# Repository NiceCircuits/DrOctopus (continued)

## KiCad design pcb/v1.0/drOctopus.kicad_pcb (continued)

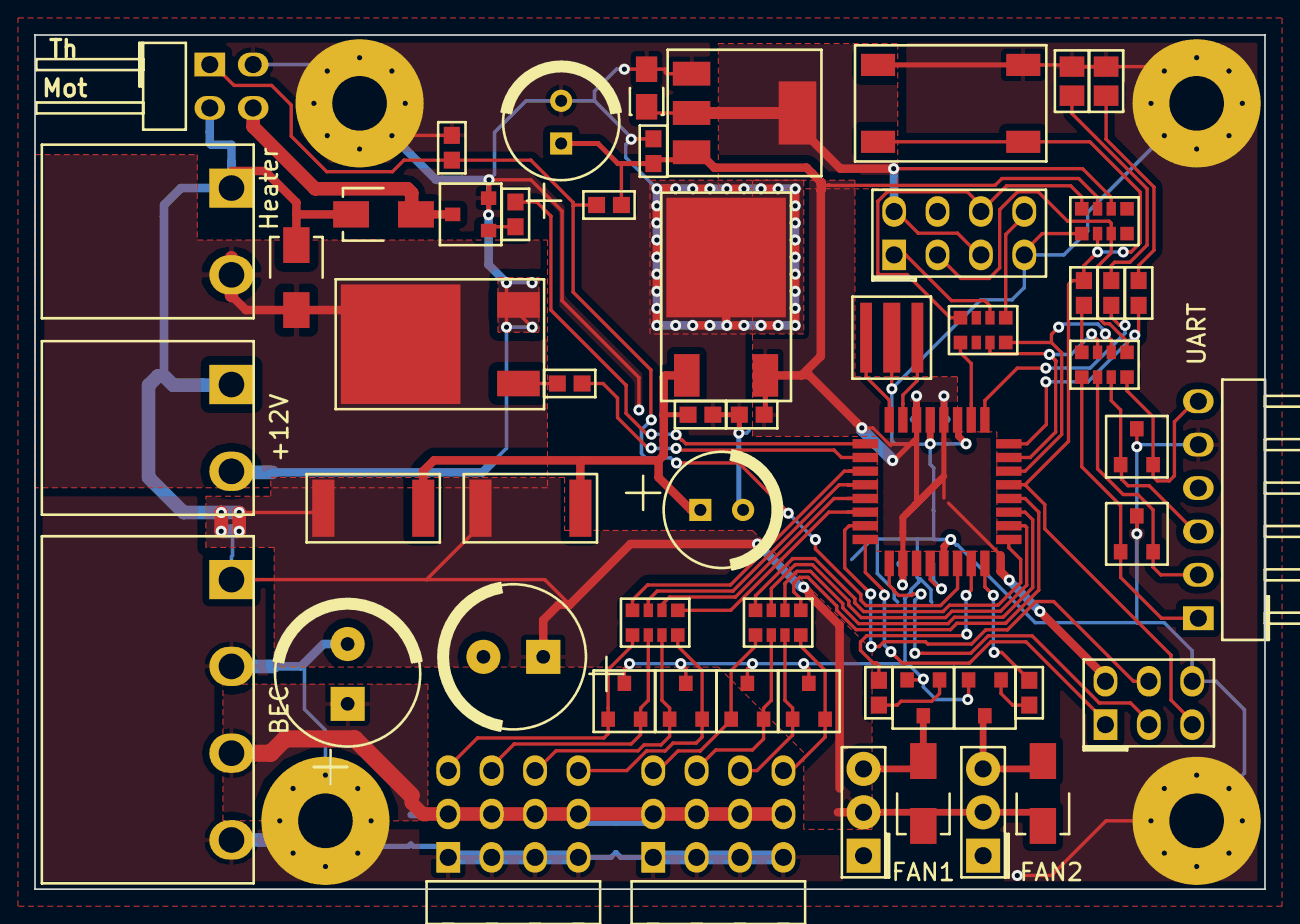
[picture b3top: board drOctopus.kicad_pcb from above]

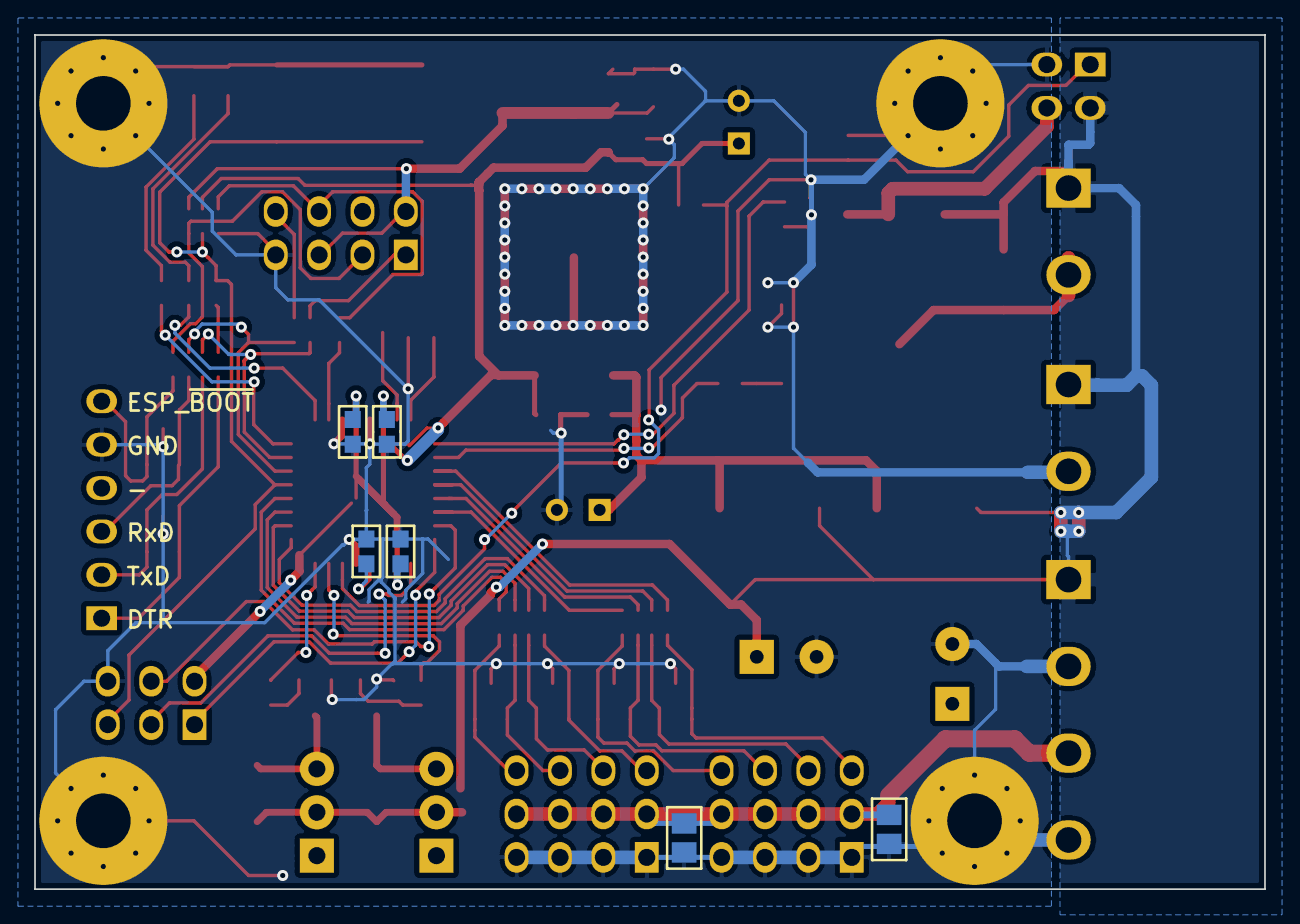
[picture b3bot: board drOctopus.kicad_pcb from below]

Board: 2 copper layers, 72.0 x 50.0 mm, 72 parts (9 on the bottom side), 58 nets.

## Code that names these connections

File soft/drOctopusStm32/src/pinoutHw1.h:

/**
 ******************************************************************************
 * @file    pinoutHw1.h
 * @author  piotr@nicecircuits.com
 * @date    2016-02-07
 * @brief   Pinout file for HW 1
 ******************************************************************************
 */
#ifndef PINOUTHW0_H_
#define PINOUTHW0_H_

#include <inttypes.h>
#include "stm32f0xx.h"
#if defined(HW_VERSION) && HW_VERSION == HW_VERSION1
/**
 * Initialize basic peripheral registers (mostly clocks and alternative pin
 * functions).
 * @return 0 if OK.
 */
uint_fast8_t portInit(void);

/**
 * Initialize ADC - version specific function.
 * @param adcBuffer ADC DMA buffer
 * @return 0 if OK
 */
uint_fast8_t adcInitVersionSpecific(uint16_t *adcBuffer);

/******************************************************************************
 * Pinout
 ******************************************************************************/
// ---------- Debug port ----------
#define DEBUG_USART USART2
#define DEBUG_GPIO GPIOA
#define DEBUG_RX_PIN GPIO_Pin_3
#define DEBUG_TX_PIN GPIO_Pin_2
#define DEBUG_DMA DMA1_Channel4
/// Debug DMA transfer complete flag.
#define DEBUG_DMA_TC_FLAG DMA1_FLAG_TC4

// ---------- LEDs ----------
/// Number of LEDs present.
#define LED_NUMBER 2
#define LED_GPIOS {GPIOB, GPIOB}
#define LED_PINS {GPIO_Pin_12, GPIO_Pin_13}
#define LED_ACTIVE_STATES {1,1}

// ---------- PWM ----------
#define PWM_TIMER TIM3
#define PWM_GPIO GPIOC
// PWM channels: motor, heater, fan, fan2
#define PWM_PINS (GPIO_Pin_9 | GPIO_Pin_6 | GPIO_Pin_7 | GPIO_Pin_8)
#define PWM_CHANNELS {&(TIM3->CCR4), &(TIM3->CCR1), &(TIM3->CCR2), &(TIM3->CCR3)}
#define PWM_IRQ TIM3_IRQn
#define PWM_IRQ_HANDLER TIM3_IRQHandler

// ---------- servos ----------
#define SERVO_NUMBER (8)
#define SERVO_TIMERS_NUMBER (4)
#define SERVO_TIMERS {TIM1, TIM15, TIM16, TIM17}
#define SERVO_GPIOS {GPIOA, GPIOA, GPIOA, GPIOA, GPIOB, GPIOB, GPIOB, GPIOB}
#define SERVO_PINS {GPIO_Pin_8, GPIO_Pin_9, GPIO_Pin_10, GPIO_Pin_11, GPIO_Pin_8, GPIO_Pin_15, GPIO_Pin_14, GPIO_Pin_9}
#define SERVO_CHANNELS {&(TIM1->CCR1), &(TIM1->CCR2), &(TIM1->CCR3), &(TIM1->CCR4), &(TIM16->CCR1), &(TIM15->CCR2), &(TIM15->CCR1), &(TIM17->CCR1)}
#define SERVO_IRQ TIM1_BRK_UP_TRG_COM_IRQn
#define SERVO_IRQ_HANDLER TIM1_BRK_UP_TRG_COM_IRQHandler

// ---------- ADC ----------
#define ADC_ADC ADC1
/// Number of ADC channels.
#define ADC_NUMBER (8)
// ADC channels: heater_sig, bts_fb_sig, thermistors from 0
#define ADC_GPIOS {GPIOA, GPIOC, GPIOA, GPIOA, GPIOC, GPIOC, GPIOC, GPIOC}
#define ADC_PINS {GPIO_Pin_5, GPIO_Pin_5, GPIO_Pin_6, GPIO_Pin_7, GPIO_Pin_4, GPIO_Pin_1, GPIO_Pin_2, GPIO_Pin_3}
#define ADC_CHANNELS {ADC_Channel_5, ADC_Channel_15, ADC_Channel_6, ADC_Channel_7, ADC_Channel_14, ADC_Channel_11, ADC_Channel_12, ADC_Channel_13}
#define ADC_DMA DMA1_Channel1
/// ADC conversion trigger event: Timer 3
#define ADC_TRIGGER (ADC_ExternalTrigConv_T3_TRGO)
#define ADC_FLAG_RDY ADC_FLAG_ADRDY
#define ADC_SAMPLE_TIME ADC_SampleTime_55_5Cycles

// ---------- I2C ----------
#define I2C I2C2
// I2C pins: SDA, SCL
#define I2C_GPIOS {GPIOB, GPIOB}
#define I2C_PINS {GPIO_Pin_11, GPIO_Pin_10}

// ---------- delay ----------
#define DELAY_TIMER TIM2

// ---------- ESP8266 ----------
#define ESP_USART USART3
#define ESP_GPIO GPIOC
#define ESP_RX_PIN GPIO_Pin_11
#define ESP_TX_PIN GPIO_Pin_10
#define ESP_EN_GPIO GPIOB
#define ESP_EN_PIN GPIO_Pin_1
#define ESP_BOOT_GPIO GPIOB
#define ESP_BOOT_PIN GPIO_Pin_0
#define ESP_TX_DMA DMA1_Channel2
/// ESP8266 DMA transmit complete flag.
#define ESP_DMA_TX_TC_FLAG DMA1_FLAG_TC2
#define ESP_IRQHandler USART3_6_IRQHandler
#define ESP_IRQ USART3_6_IRQn
#else // #if defined(HW_VERSION) && HW_VERSION == HW_VERSION1
#error "Invalid pinout file used or HW version not defined!"
#endif
#endif /* PINOUTHW0_H_ */

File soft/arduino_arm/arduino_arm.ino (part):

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#include <EEPROM.h>
#define HDServoMode 20
#define SerialInterfaceSpeed 115200    // Serial interface Speed
#define THERM A7
#define HEAT 6
#define MOT 5
#define LED 3

static unsigned int iCount;
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void setup()
{
 uint8_t id = EEPROM.read(10);
 pinMode(HEAT, OUTPUT);
  pinMode(MOT, OUTPUT);
 pinMode(THERM, INPUT);
 if (id==4)
 {
  OutPortTable = OutPortTable4;
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
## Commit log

2014-08-02 Start design
2014-08-03 Select motors
2014-08-03 Sketches
2014-10-09 Start 3D modeling
2014-10-10 Straight version
2014-10-10 3D design
2014-10-12 Continue 3D modeling
2014-10-13 Fix small issues
2014-10-20 3D modeling
2014-10-21 Soft
2014-10-22 Rename and generate production files
2015-08-27 Nowa PCB - wersja robocza
2015-08-31 Working on new PCB
2015-09-01 PCB ready to be sent
2015-11-10 Last commit for this version
2015-11-10 Clean previous version of software. Starting again.
2015-11-10 First test software for MQTT for Python (Spyder) and Arduino (Eclipse).
2015-11-12 Test software.
2015-11-12 Beginning of main Arduino software
2015-11-13 Add oled test
2015-11-14 New, lighter OLED library test.
2015-11-14 Better support of OLED and Wifi. Reformat. Program: 26806 bytes (81.8% Full) Data: 1616 bytes (78.9% Full)
2015-11-15 Switch all String to char*. Decrease espduino buffer size (in library). Program: 24940 bytes (76.1% Full) Data: 1361 bytes (66.5% Full)
2015-11-15 Test oled. Remove some used fonts to conserve program memory.
2015-11-15 Remove some used fonts to conserve program memory. Change baudrate. Reformat.
2015-11-15 Update ignore list
2015-11-15 Rename. Reformat. Python mqtt test small change.
2015-11-24 Add debug options: software serial/ hardware serial/ none.
2015-11-24 Add servos
2015-11-24 Tweaks of Wifi
2015-11-24 Add MQTT receiver python script
2015-11-27 Change some net names
2015-11-27 Add debugPin function.
2015-11-27 Add circular command buffer
2015-11-29 Add functions to synchronize time.
2015-11-29 Fix debugPin functions
2015-11-29 Fix command buffer.
2015-11-29 Debug functions to see time passing
2015-11-29 Improve servos driver
2015-11-29 Improve mqtt topic settings
2015-11-29 Add time synchronize functionality
2015-12-12 Add little debug functions
2015-12-13 Added usage of program memory for strings. Global variables size reduction: - Without debug: 1520 -> 1383 (program 21348 -> 21490) - With debug, hardware uart: 1642 -> 1401 (program 22040 -> 22294)
2015-12-20 Add buffer for OLED strings
2015-12-20 Add SPI debug mode
2016-01-23 Some missing files
2016-01-23 Base of ne PCB design - two PCBs
2016-01-23 Clean and rename
2016-01-24 Working on Power PCB
2016-01-28 Working on PCBs
2016-01-28 Schematic polishing
2016-02-01 PCB routing
2016-02-02 License change
2016-02-04 Probably final version of PCBs
2016-02-04 Little fix of silkscreen
2016-02-04 Last corrections. Gerber generation.
2016-02-04 Mechanical parts added
2016-02-06 Remove old version of controller firmware (Arduino). Add new blank project for new version of controller firmware (STM32 using System Workbench for STM32).
2016-02-06 Remove old version of controller firmware (Arduino). Add new blank test project for STM32.
2016-02-07 Blink test. Remove some unnecessary files.
2016-02-07 Add config files.
2016-02-07 Debug USART configuration.
2016-02-08 Add basic outputs module with LED driver
2016-02-08 Add sysTick module with delayMs function.
2016-02-08 Basic DMA configuration for debug UART.
2016-02-09 debugPrint function with DMA and printf-like formatting.
2016-02-09 Add multiple sources handling to debug function.
2016-02-11 Add PWM driver. Refactor peripheral clock setup functions.
2016-02-13 Refactor uint_8_t -> uint_fast8_t as output code in some functions.
2016-02-13 Add servo driver. Refactor uint_8_t -> uint_fast8_t as output code in some functions.
2016-02-14 Working on servo driver.
2016-02-14 Add interrupt handlers to vector table.
2016-02-14 Add interrupt handler to vector table.
2016-02-15 Add getTime function.
2016-02-15 Update servo driver. Add speed control.
2016-02-15 Simple ADC driver.
2016-02-16 ADC with DMA transfer.
2016-02-16 Configure ADC to convert on PWM_TIMER update.
2016-02-19 Add HW0 pinout to Excel sheet.
2016-02-19 Add simple I2C init.
2016-02-19 Add some check to init function.
2016-02-21 Rename sysTick.c ->delay.c. Add delayUs function, using standard timer. Add DELAY_TEST build configuration with test for delay functions.
2016-02-21 Optimize delayUs function. Led pulse length for delayUs(1): 3.98us -> 3.32us
2016-02-21 Optimize delayUs test function. Led pulse length for delayUs(1): 3.32us -> 2.96us.
2016-02-21 Optimize delayUs test function. Led pulse length for delayUs(1): 2.96us -> 2.70us.
2016-02-21 Optimize delayUs test function. Led pulse length for delayUs(1): 2.70us -> 2.50us.
2016-02-21 Fix delayUs function. Led pulse length for delayUs(1): 2.50us -> 1.53us.
2016-02-21 Rewrite delayMs function. Minor improvements.
2016-02-22 Move license file.
2016-02-22 Update pinout calculations.
2016-02-22 Start porting u8glib to drive OLED display.
2016-02-22 Remove unneeded file.
2016-02-22 Update u8glib to newest version.
2016-02-27 New timer functions.
2016-02-27 New test build configurations.
2016-02-27 Add LEDs to pinout HW0.
2016-02-27 Move design files.
2016-02-27 Writing functions needed by u8glib.
2016-02-27 Update delay test.
2016-02-27 Simple I2C driver: transmit.
2016-02-27 Change some #defines to enums.
2016-02-27 Remove u8glib examples.
2016-02-27 Debug: wait until previous print is complete. Add debug test build configuration.
2016-02-28 Working on I2C driver. Dead end, will be corrected.
2016-02-28 I2C driver cleanup.
2016-02-29 Remove unused files.
2016-02-29 Simple software I2C driver instead of shitty STM32 hardware one.
2016-02-29 Oled driver.
2016-03-13 Add BOM.
2016-03-13 Change annotations on schematic.
2016-03-13 Pinout for uC change in HW1 (STM32F030RCT6).
2016-03-13 Start writing ESP8266 driver.
2016-03-14 Add esp-link client library.
2016-03-17 Work on redesigning ElClient library.
2016-03-21 Work on redesigning ElClient library. Refactor.
2016-03-21 Building ESP8266 driver.
2016-03-21 Library object constructor fix.
2016-03-21 Working ESP8266 MQTT driver.
2016-03-22 Replace StdPeriph_Driver with version for HW1.
2016-03-22 Move project to HW1 platform.
2016-03-24 Restore and add test firmware build configurations.
2016-04-02 Add #ifs to improve Eclipse indexing.
2016-04-02 Debug test working on HW1.
2016-04-02 Cosmetic fix (preprocessor syntax and error message).
2016-04-02 Little fix of delay test. Add comments. Delay test working for HW1.
2016-04-02 Lower PWM frequency to 200Hz - higher not necessary.
2016-04-02 Add outputs test. Fix PWM initialization. Outputs test working for HW1.
2016-04-03 Remove unnecessary file.
2016-04-03 Change debug, optimization and warning flags.
2016-04-03 Add debugPrintRaw function to print debug without prefix and newline.
2016-04-03 Fix PWM IRQ configuration.
2016-04-03 Fix ADC configuration. Add ADC test firmware. Test working with HW1.
2016-04-03 Little fix of TEST_MODE selection #if command.
2016-04-04 Add Default_Handler and HardFault_Handler with blinking leds.
2016-04-04 Fix some implicit conversion warnings.
2016-04-04 Pinout update.
2016-04-04 Cosmetic changes of annotations to improve readability.
2016-04-04 Remove old project.
2016-04-04 Ignore "old" folder.
2016-04-04 Working on ESP8266 driver on HW1. Fix some implicit conversion compiler warnings (and some real errors too). Add programming mode - pipe between ESP USART and debug USART.
2016-04-04 Fix some implicit conversion and unused parameter warnings.
